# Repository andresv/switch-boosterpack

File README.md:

## Switch Launchpad Boosterpack

This is boosterpack for MSP430 Launchpad. It has SSD1306 based 128x64 pixel OLED display and 4 power MOSFET outputs. It is meant for switching various loads - for example pneumatic actuators or relays.

Software is written using Energia: https://github.com/energia/Energia

## LICENSE
### Software
This work is licensed under MIT license. http://opensource.org/licenses/MIT
### Hardware
This work is licensed under version 3.0 of the Creative Commons CC-BY-SA license.
http://creativecommons.org/licenses/by-sa/3.0/

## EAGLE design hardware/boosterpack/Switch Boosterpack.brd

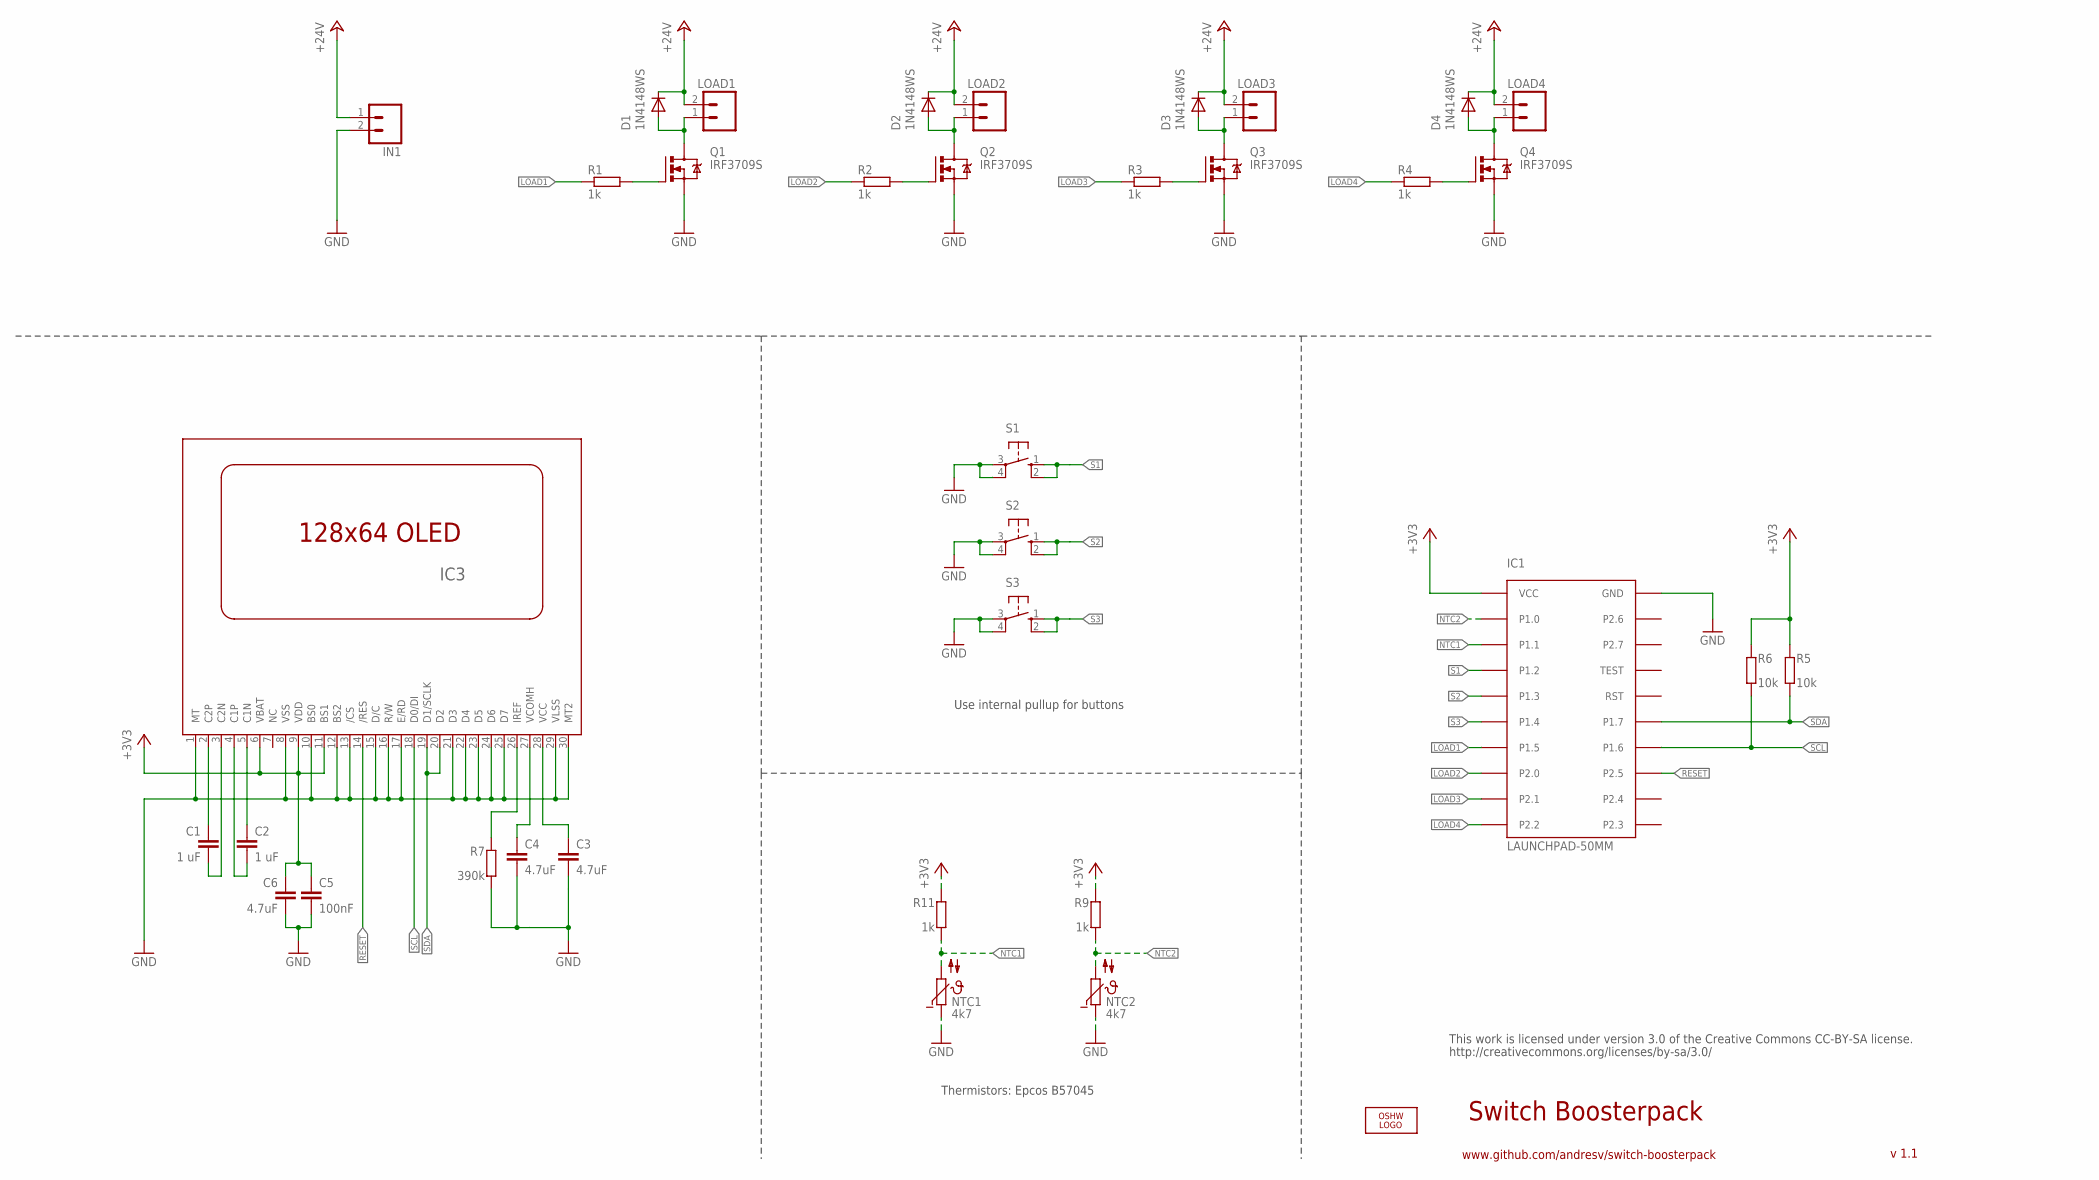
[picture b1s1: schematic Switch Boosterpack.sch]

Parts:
C1, C2: 1 uF; C0603
C3, C4, C6: 4.7uF; C0603
C5: 100nF; C0603
D1, D2, D3, D4: 1N4148WS; SOD323-W
IC1: LAUNCHPAD-50MM
IC3: UG-2864HSWEG01; 1X30-0.7MM
IN1: M025MM; SCREWTERMINAL-5MM-2
LOAD1, LOAD2, LOAD3, LOAD4: M025MM; SCREWTERMINAL-5MM-2
LOGO1: OSHW_LOGO_8MILX0350-NT; OSHW_8X350_NOTEXT
NTC1, NTC2: 4k7; N640
Q1, Q2, Q3, Q4: IRF3709S; D-PAK_TO252AA
R1, R2, R3, R4, R9, R11: 1k; R0603
R5, R6: 10k; R0603
R7: 390k; R0603
S1, S2, S3: 10-XX; B3F-10XX

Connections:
+3V3: C5.1, C6.1, IC1.VCC, IC3.6 (VBAT), IC3.9 (VDD), IC3.11 (BS1), R5.2, R6.2, R9.2, R11.2
+24V: D1.C, D2.C, D3.C, D4.C, IN1.1, LOAD1.2, LOAD2.2, LOAD3.2, LOAD4.2
GND: C3.2, C4.2, C5.2, C6.2, IC1.GND, IC3.1 (MT), IC3.8 (VSS), IC3.10 (BS0), IC3.12 (BS2), IC3.13 (/CS), IC3.15 (D/C), IC3.16 (R/W), IC3.17 (E/RD), IC3.21 (D3), IC3.22 (D4), IC3.23 (D5), IC3.24 (D6), IC3.25 (D7), IC3.29 (VLSS), IC3.30 (MT2), IN1.2, NTC1.1, NTC2.1, Q1.3 (S), Q2.3 (S), Q3.3 (S), Q4.3 (S), R7.1, S1.3, S1.4 (P1), S2.3, S2.4 (P1), S3.3, S3.4 (P1)
LOAD1: IC1.P1.5, R1.1
LOAD2: IC1.P2.0, R2.1
LOAD3: IC1.P2.1, R3.1
LOAD4: IC1.P2.2, R4.1
unnamed: D1.A, LOAD1.1, Q1.4 (D)
unnamed: Q1.1 (G), R1.2
unnamed: D2.A, LOAD2.1, Q2.4 (D)
unnamed: Q2.1 (G), R2.2
unnamed: D3.A, LOAD3.1, Q3.4 (D)
unnamed: Q3.1 (G), R3.2
unnamed: D4.A, LOAD4.1, Q4.4 (D)
unnamed: Q4.1 (G), R4.2
unnamed: C1.1, IC3.2 (C2P)
unnamed: C1.2, IC3.3 (C2N)
unnamed: C2.1, IC3.5 (C1N)
unnamed: C2.2, IC3.4 (C1P)
unnamed: C3.1, IC3.28 (VCC)
unnamed: C4.1, IC3.27 (VCOMH)
unnamed: IC3.26 (IREF), R7.2
NTC1: IC1.P1.1, NTC1.2, R11.1
NTC2: IC1.P1.0, NTC2.2, R9.1
RESET: IC1.P2.5, IC3.14 (/RES)
S1: IC1.P1.2, S1.1 (S), S1.2 (S1)
S2: IC1.P1.3, S2.1 (S), S2.2 (S1)
S3: IC1.P1.4, S3.1 (S), S3.2 (S1)
SCL: IC1.P1.6, IC3.18 (D0/DI), R6.1
SDA: IC1.P1.7, IC3.19 (D1/SCLK), IC3.20 (D2), R5.1

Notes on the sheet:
Switch Boosterpack
www.github.com/andresv/switch-boosterpack
v 1.1
This work is licensed under version 3.0 of the Creative Commons CC-BY-SA license.
http://creativecommons.org/licenses/by-sa/3.0/
Thermistors: Epcos B57045
Use internal pullup for buttons

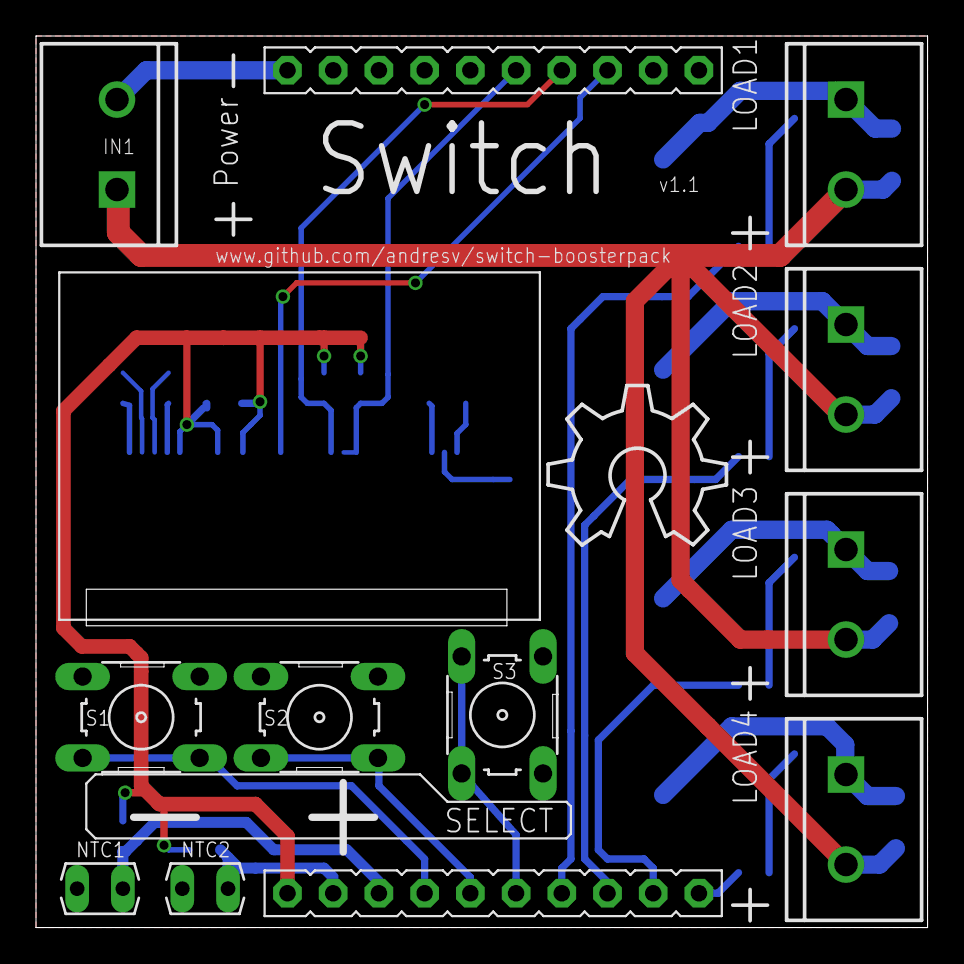
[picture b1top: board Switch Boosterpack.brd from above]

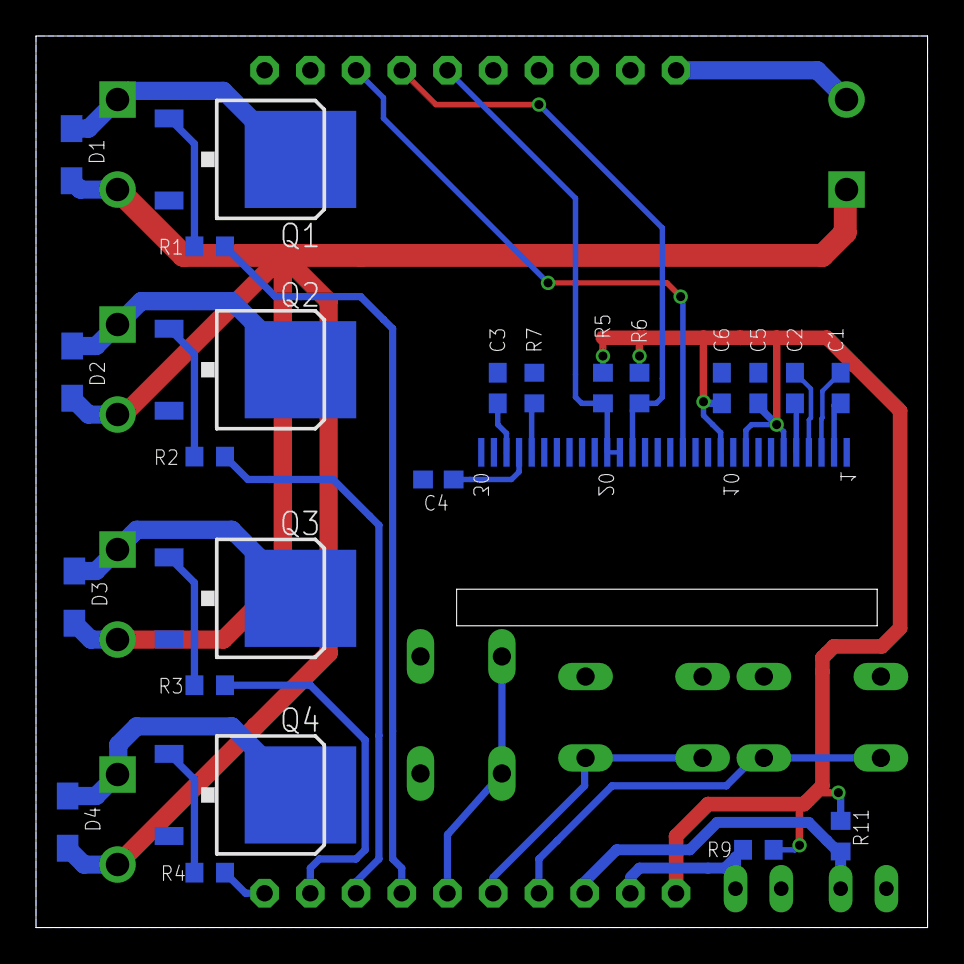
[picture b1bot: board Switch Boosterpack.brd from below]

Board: 2 copper layers, 49.5 x 49.5 mm, 36 parts (23 on the bottom side), 30 nets.

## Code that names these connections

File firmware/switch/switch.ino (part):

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#define PLUS_BUTTON 4
#define MINUS_BUTTON 5
#define SELECT_BUTTON 6
#define LOAD1 7
#define LOAD2 8
#define LOAD3 9
#define LOAD4 10

#define NUMTEMPS 103 // NTC table
#define ROLLING_AVERAGE_SIZE 10
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
    display_temperature();

    pinMode(LOAD1, OUTPUT);
    pinMode(LOAD2, OUTPUT);
    pinMode(LOAD3, OUTPUT);
    pinMode(LOAD4, OUTPUT);
    switch_relay(1, OFF);
    switch_relay(2, OFF);
    switch_relay(3, OFF);
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
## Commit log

2012-09-23 Added initial EAGLE schematic and board files.
2012-09-23 Added hardware license file.
2012-10-20 Tweaked silkscreen and made OLED ribbon cutoff longer.
2012-10-21 Fixed load 1 + sign position.
2012-10-21 BS0 is now tied to GND, C1, C2 are 1 uF and R7 is 390k.
    Those are main v1.0 errors. They must be fixed otherwise v1.0 boards are not working.
2012-10-21 Added initial firmware.
    OLED driver for Energia environment is working.
2012-10-25 Added padding to format strings.
    printf(" %4u", 56);
    printf(" %4i", -56);
2012-10-25 Initial user interface with buttons ready.
2012-10-25 Fixed typo in README
2012-11-01 Fixed schematic, instead of N channel FET there were P channel FET on schematic.
    So actually 1.0 board MOSFET side was messed up. Now it is correct. P channel FET was used in "N channel configuration".
2012-11-06 Added NTC temperature sensor readings.
2012-11-06 Now set temperature parameters are saved to flash.
2012-11-07 Now 10 element average temperature is shown to reduce jumping.
2012-11-07 Fixed typo in average calculation.
2012-11-07 Added MOSFET switching to switch_relay(..) function.
2012-11-07 Made UI little bit nicer.
2012-11-07 Added on/off regulator with hysteresis.
2012-11-10 Added garage specific branch.
2012-11-10 Now relay of/off switching works.
2012-11-10 Now relays 1 and 2 go off if 60 minutes is passed.

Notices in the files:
firmware/switch/switch.ino:
Copyright 2012 Andres Vahter
